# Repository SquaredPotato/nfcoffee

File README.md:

# nfcoffee

### Vind jij de koffiemachines op de hva ook zo tergend langzaam dat je al je haren er 's ochtends uit wil trekken als je meer dan 2 bakkies haalt 

# wij dus ook!!

## daarom hebben we nu NFCoffee zodat je snel met je persoonlijke koffiebeker je favoriete bakkie pleur kan bestellen

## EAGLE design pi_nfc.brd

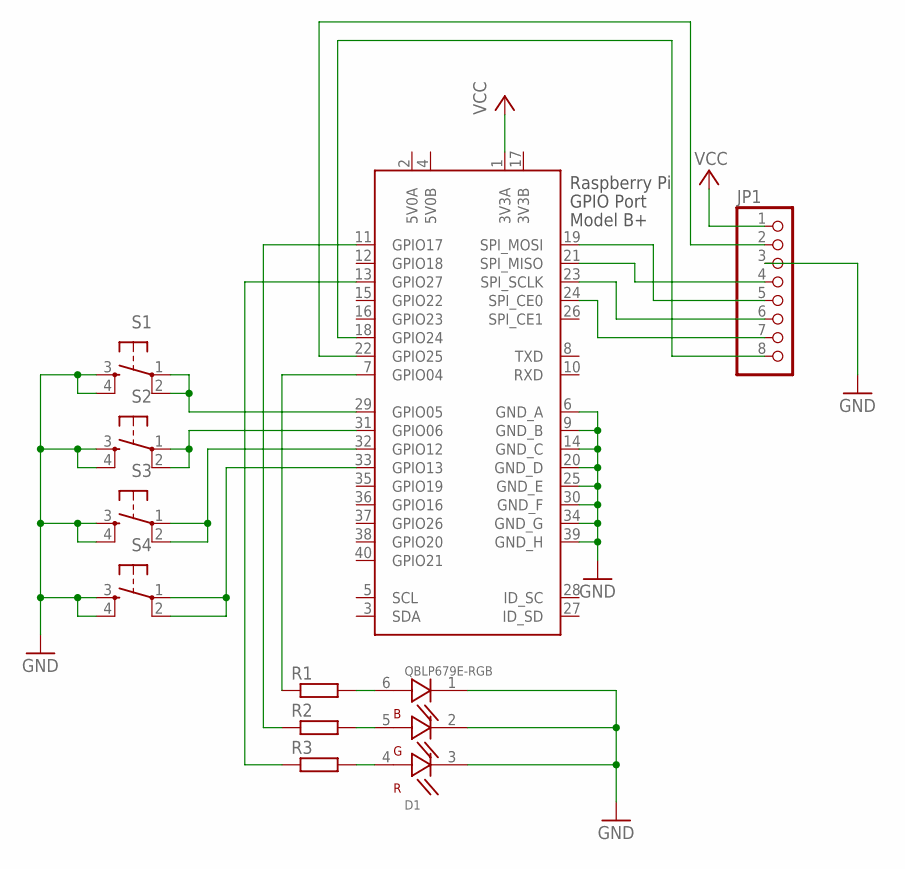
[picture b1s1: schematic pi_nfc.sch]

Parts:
D1: QBLP679E-RGB; LED_QBLP679E-RGB
JP1: PINHD-1X8; 1X08
R1, R2, R3: R-EU_M0805; M0805
S1, S2, S3, S4: TAC_SWITCHPTH; TACTILE-PTH
X1: RASPI_GPIO_B+#_PIN; RASPI_GPIO_B+_PIN

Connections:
3V3B: X1.17 (3V3B)
5V0A: X1.2 (5V0A)
5V0B: X1.4 (5V0B)
GND: D1.1 (BC), D1.2 (GC), D1.3 (RC), JP1.3, S1.3, S1.4, S2.3, S2.4, S3.3, S3.4, S4.3, S4.4, X1.6 (GND_A), X1.9 (GND_B), X1.14 (GND_C), X1.20 (GND_D), X1.25 (GND_E), X1.30 (GND_F), X1.34 (GND_G), X1.39 (GND_H)
unnamed: JP1.2, X1.22 (GPIO25)
unnamed: D1.6 (BA), R1.2
unnamed: D1.5 (GA), R2.2
unnamed: D1.4 (RA), R3.2
unnamed: R1.1, X1.7 (GPIO04)
unnamed: JP1.4, X1.21 (SPI_MISO)
unnamed: JP1.5, X1.19 (SPI_MOSI)
unnamed: JP1.6, X1.23 (SPI_SCLK)
unnamed: JP1.7, X1.24 (SPI_CE0)
unnamed: JP1.8, X1.18 (GPIO24)
unnamed: R2.1, X1.11 (GPIO17)
unnamed: R3.1, X1.13 (GPIO27)
unnamed: S1.1, S1.2, X1.29 (GPIO05)
unnamed: S2.1, S2.2, X1.31 (GPIO06)
unnamed: S3.1, S3.2, X1.32 (GPIO12)
unnamed: S4.1, S4.2, X1.33 (GPIO13)
VCC: JP1.1, X1.1 (3V3A)

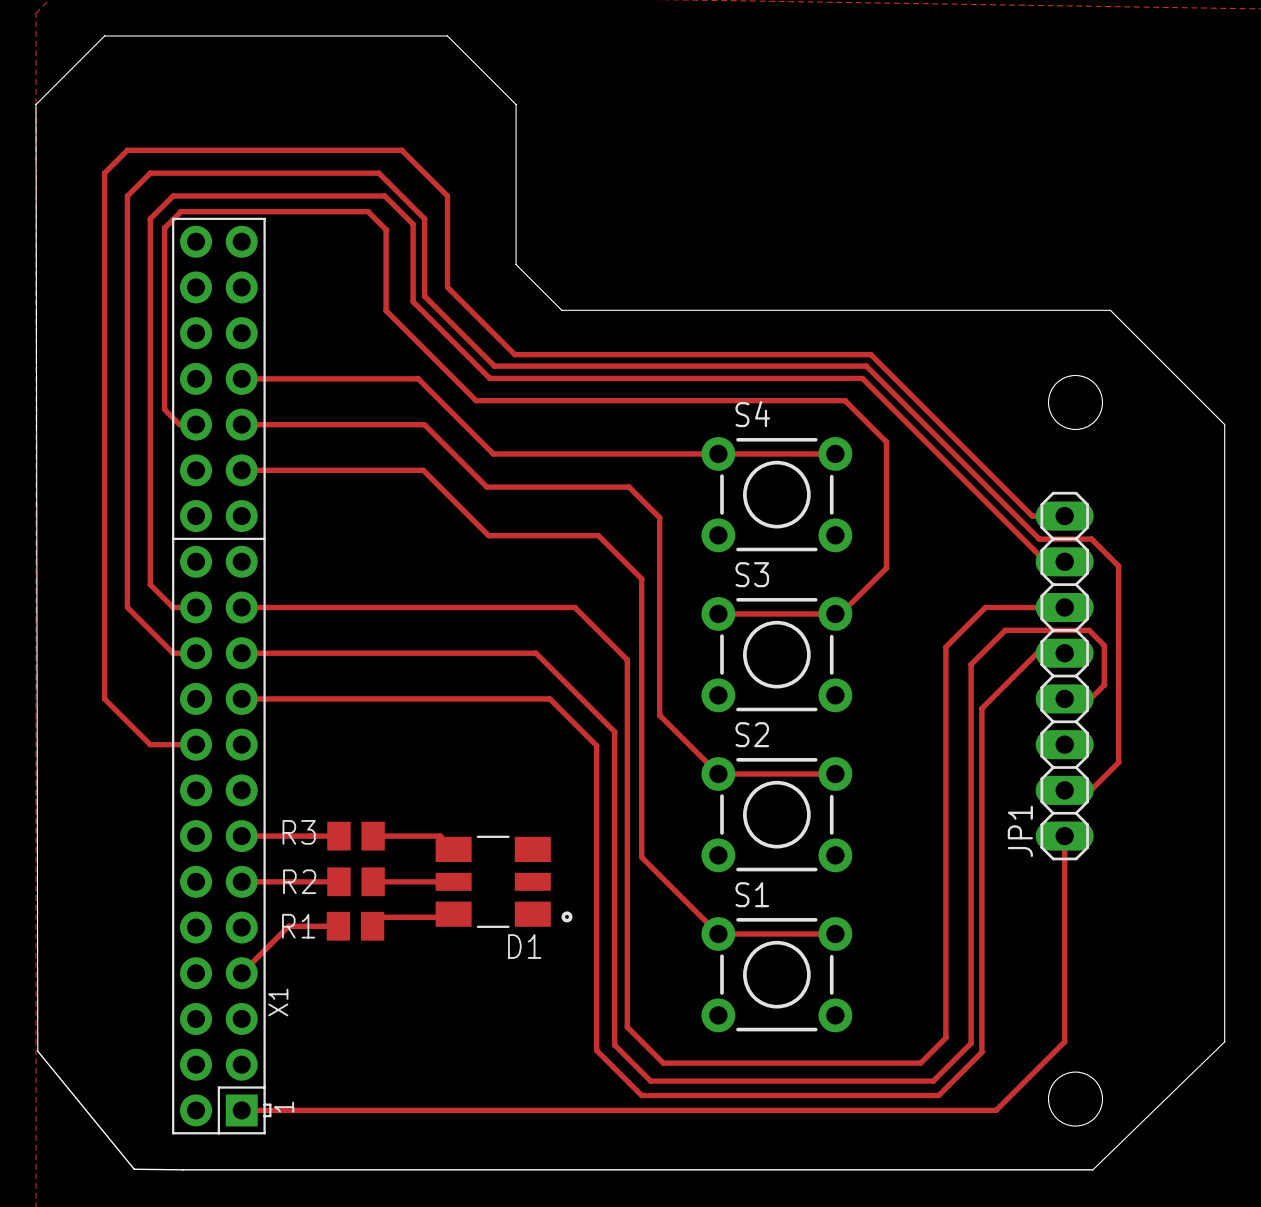
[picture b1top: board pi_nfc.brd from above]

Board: 2 copper layers, 66.0 x 63.0 mm, 10 parts (0 on the bottom side), 18 nets.

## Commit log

2019-09-16 test for bram
2019-09-17 Read NFC card
2019-09-17 Printed Circuit Boards
    eagle pcb files
2019-09-17 writing nfc
2019-09-17 Schema werking interface
    en de directory een beetje opgeschoond
2019-09-17 added recipe crafter class, converted nfc utilities into class
2019-09-18 Led button interface added
    First build up button interface
2019-09-18 Fixed bugs, tighter integration between recipe and reader class
2019-09-19 bugfixes
2019-09-19 Presentatie
    LaTeX presentation added
2019-09-19 Smaal change eagle & interface set up NFCoffee
2019-09-19 whoops, sorry
    Forgot delete folder
2019-09-19 removed useless LaTeX files
2019-09-20 delivery

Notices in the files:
parts and their libraries:
SparkFun-Electromechanical: Licensing: CC v3.0 Share-Alike You are welcome to use this library for commercial purposes.
